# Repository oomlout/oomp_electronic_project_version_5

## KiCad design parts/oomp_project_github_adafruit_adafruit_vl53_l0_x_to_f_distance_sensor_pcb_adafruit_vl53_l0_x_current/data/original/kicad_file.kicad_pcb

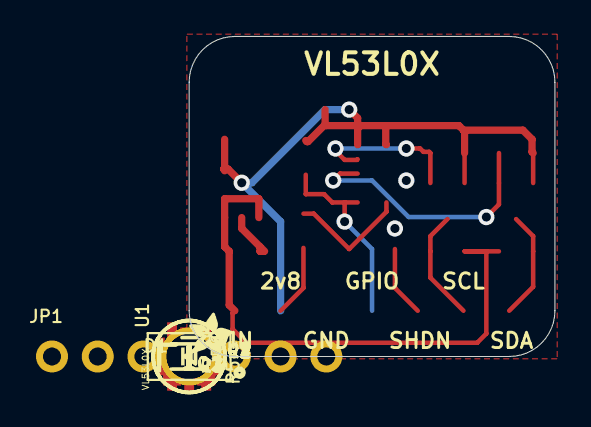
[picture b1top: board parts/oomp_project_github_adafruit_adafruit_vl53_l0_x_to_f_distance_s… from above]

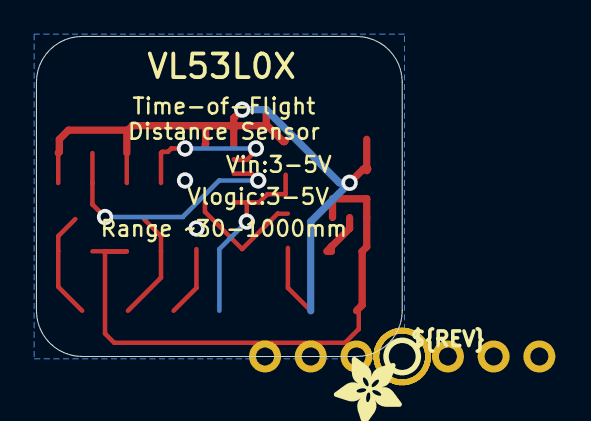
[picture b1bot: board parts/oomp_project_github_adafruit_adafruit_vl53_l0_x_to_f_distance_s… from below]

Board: 2 copper layers, 20.3 x 17.8 mm, 22 parts (2 on the bottom side), 10 nets.

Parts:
C1, C2: 10µF; 0805-NO
C3: 0.1uF; 0805-NO
D1: 1N4148; SOD-323
FID2, FID3: FIDUCIAL""; FIDUCIAL_1MM
JP1: 1X07_ROUND_70
Q1, Q2: BSS138; SOT23-WIDE
R1, R2, R3, R4, R5, R6: 10K; 0805-NO
U1: VL53L0X; LGA12_ST
U2: MIC5225_2.8V; SOT23-5
U$12: PCBFEAT-REV-040
U$13, U$14: MOUNTINGHOLE2.5; MOUNTINGHOLE_2.5_PLATED
U$15: ADAFRUIT_3.5MM
U$18: ADAFRUIT_2.5MM

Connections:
2.8V: C2.1, C3.1, JP1.2, Q1.1, Q2.1, R1.2, R2.2, R5.2, R6.2, U1.1, U1.11, U2.5
GND: C1.2, C2.2, C3.2, JP1.3, U1.2, U1.3, U1.4, U1.6, U1.12, U2.2
GPIO: JP1.4, R6.1, U1.7
SCL: JP1.6, Q2.3, R4.1
SCL_2.8V: Q2.2, R2.1, U1.10
SDA: JP1.7, Q1.3, R3.1
SDA_2.8V: Q1.2, R1.1, U1.9
VIN: C1.1, JP1.1, R3.2, R4.2, U2.1, U2.3
XSHUT: D1.C, JP1.5
XSHUT_2.8V: D1.A, R5.1, U1.5

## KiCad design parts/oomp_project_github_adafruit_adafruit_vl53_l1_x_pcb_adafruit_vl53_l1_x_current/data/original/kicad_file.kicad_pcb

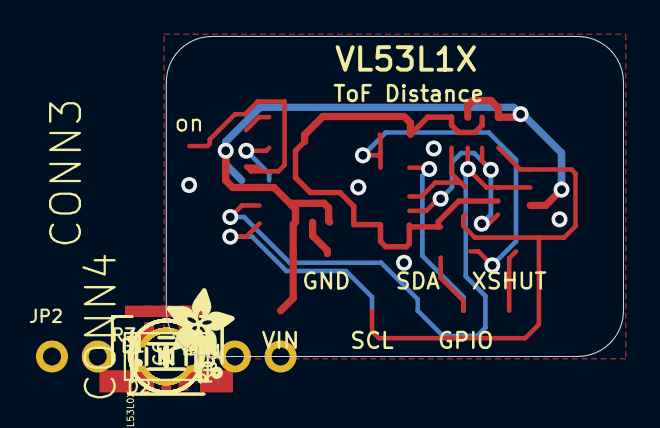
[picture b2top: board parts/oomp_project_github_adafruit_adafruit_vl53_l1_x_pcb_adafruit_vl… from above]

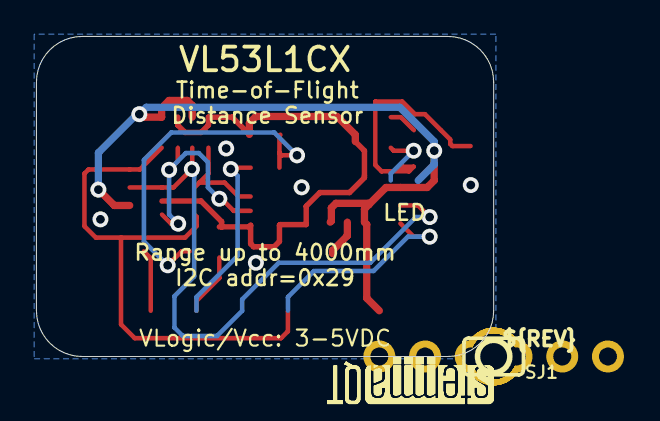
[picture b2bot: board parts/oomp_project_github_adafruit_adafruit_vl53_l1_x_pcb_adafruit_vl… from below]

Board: 2 copper layers, 25.4 x 17.8 mm, 26 parts (4 on the bottom side), 12 nets.

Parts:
C4, C5: 10uF; 0805-NO
C6: 0.1uF; 0603-NO
CONN3, CONN4: STEMMA_I2C_QT; JST_SH4
D1: 1N4148; SOD-323
D2: GREEN; CHIPLED_0603_NOOUTLINE
FID1, FID4: FIDUCIAL_1MM
JP2: 1X06_ROUND_70
Q3: BSS138; SOT363
R1, R2, R3: 10K; 0603-NO
R7: 10K; RESPACK_4X0603
SJ1: SOLDERJUMPER_CLOSEDWIRE
U1: VL53L0X; LGA12_ST
U3: LP5907-2.8; SOT23-5
U$30, U$31, U$33, U$34: MOUNTINGHOLE2.5; MOUNTINGHOLE_2.5_PLATED
U$36: ADAFRUIT_3.5MM
U$37: PCBFEAT-REV-040
U$38, U$39: STEMMAQT

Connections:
2.8V: C5.1, C6.1, Q3.2, Q3.5, R1.2, R2.2, R7.2, R7.4, U1.1, U1.11, U3.5
GND: C4.2, C5.2, C6.2, CONN3.1, CONN3.MT1, CONN3.MT2, CONN4.1, CONN4.MT1, CONN4.MT2, D2.C, JP2.2, U1.2, U1.3, U1.4, U1.6, U1.12, U3.2
GPIO: JP2.5, R2.1, U1.7
unnamed: D2.A, R3.1
unnamed: R3.2, SJ1.1
SCL: CONN3.4, CONN4.4, JP2.3, Q3.6, R7.8
SCL_3V: Q3.1, R7.7, U1.10
SDA: CONN3.3, CONN4.3, JP2.4, Q3.3, R7.6
SDA_3V: Q3.4, R7.5, U1.9
VCC: C4.1, CONN3.2, CONN4.2, JP2.1, R7.1, R7.3, SJ1.2, U3.1, U3.3
XSHUT: D1.C, JP2.6
XSHUT_2.8V: D1.A, R1.1, U1.5

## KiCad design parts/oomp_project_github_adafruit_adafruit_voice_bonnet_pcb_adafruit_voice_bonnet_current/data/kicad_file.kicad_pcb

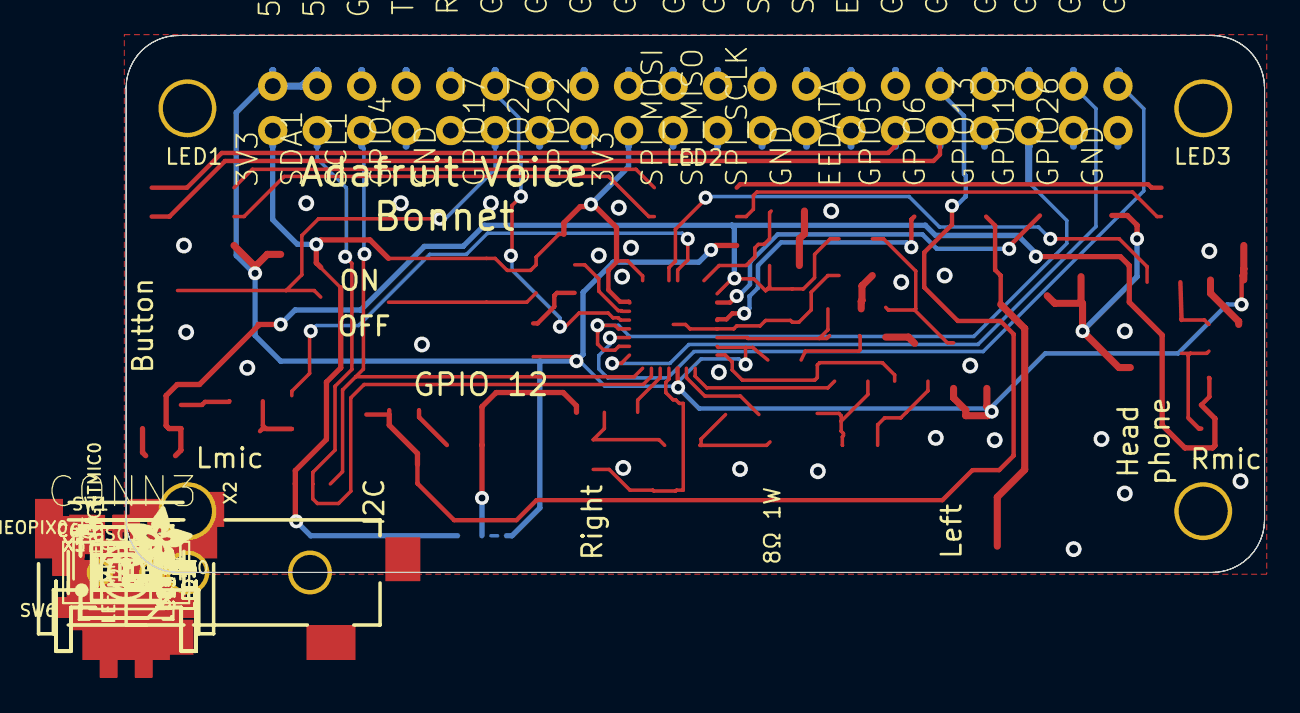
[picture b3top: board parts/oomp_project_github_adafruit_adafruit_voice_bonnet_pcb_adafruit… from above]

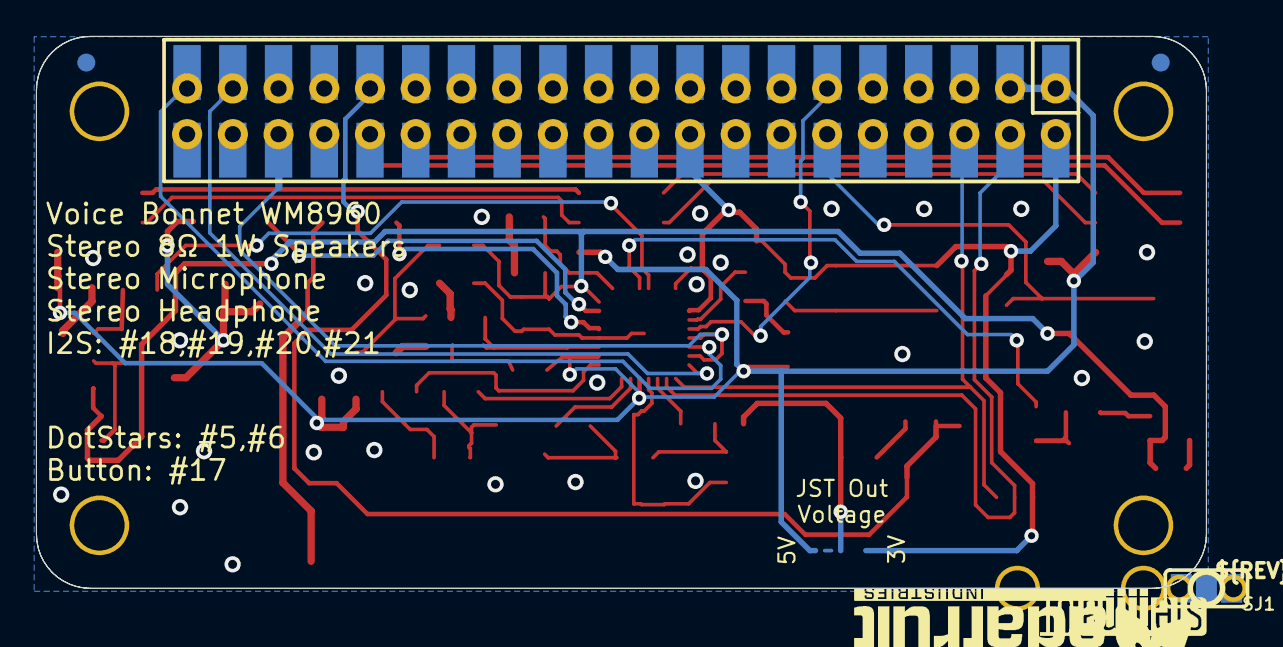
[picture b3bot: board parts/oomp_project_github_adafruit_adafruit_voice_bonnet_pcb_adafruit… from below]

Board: 2 copper layers, 65.0 x 30.7 mm, 69 parts (5 on the bottom side), 62 nets.

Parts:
C1, C2, C5, C9, C10, C11, C13, C23, C24, C32, C34: 10uF; 0805-NO
C3, C7, C8, C12, C14, C16, C18, C25: 0.1uF; 0603-NO
C4, C6: 100uF; PANASONIC_C
C19, C20, C21, C22: 33pF; 0603-NO
C26, C27: 220pF; 0603-NO
C28, C29, C30, C31: 100pF; 0603-NO
C33: 2.2uF+; 0805-NO
CONN3: STEMMA_I2C_QT; JST_SH4
D1: 3.6V; SOD-323
FB1, FB2: Ferrite; 0805
FB3: Ferrite; 0805-NO
FB4: FERRITE; 0805-NO
FB7, FB8, FB9, FB10: 120o; 0805-NO
FID1, FID2: FIDUCIAL_1MM
IC3: WM8960; QFN32_5MM
LED1, LED2, LED3: SK6822; APA102
LEFTMIC0: SPW2430HR5H-B
NEOPIX0: JST PH 3; JSTPH3
OSC1: ECS-3225MV; OSC_3.2X2.5MM
R1, R4: 10K; 0603-NO
R6: 10k; 0603-NO
R7: 1K; 0603-NO
RIGHTMIC0: SPW2430HR5H-B
RPI1: RASPBERRYPI_BPLUS_BONNET_THMSMT; PI_BONNET_THMSMT
SJ1: SOLDERJUMPER_2WAY_OPEN_NOPASTE
SW1: EVQQ; EVQ-Q2_SMALLER
SW6: EG1390
U3: AP2112-3.3K; SOT23-5
U$11: PCBFEAT-REV-040
U$12: STEMMAQT
U$15: ADAFRUIT_3.5MM
U$16: ADAFRUIT_TEXT_20MM
U$79: BRAINPAD_1IN
X1, X5: JSTPH 2P; JSTPH2
X2: 3.5mm; 4UCONN_19269

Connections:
3.3V: C12.1, CONN3.2, IC3.8, IC3.10, OSC1.4, R1.2, RPI1.1, RPI1.17, RPI1.S1, RPI1.S17, SJ1.3, SW6.S1, SW6.S2
5.0V: C9.1, C10.1, C11.1, C32.1, C33.1, IC3.21, IC3.26, LED1.4, LED2.4, LED3.4, RPI1.2, RPI1.4, RPI1.S2, RPI1.S4, SJ1.1, U3.1, U3.3
AGND: C3.2, C5.2, FB2.1, IC3.28, IC3.33
AVDD: C3.1, C5.1, C16.1, C18.1, C25.1, FB1.1, IC3.32, LEFTMIC0.4, RIGHTMIC0.4
BUTTON: R1.1, RPI1.11, RPI1.S11, SW1.B, SW1.B'
CE0: RPI1.24, RPI1.S24
CE1: RPI1.26, RPI1.S26
EEC: RPI1.28, RPI1.S28
EED: RPI1.27, RPI1.S27
GND: C1.2, C2.2, C7.2, C8.2, C9.2, C10.2, C11.2, C12.2, C13.2, C14.2, C16.2, C18.2, C19.2, C20.2, C21.2, C22.2, C25.2, C26.2, C27.2, C28.2, C29.2, C30.2, C31.2, C32.2, C33.2, C34.2, CONN3.1, D1.A, FB2.2, IC3.9, IC3.20, IC3.24, LED1.3, LED2.3, LED3.3, LEFTMIC0.2, LEFTMIC0.3, NEOPIX0.1, OSC1.2, R4.1, R6.1, RIGHTMIC0.2, RIGHTMIC0.3, RPI1.6, RPI1.9, RPI1.14, RPI1.20, RPI1.25, RPI1.30, RPI1.34, RPI1.39, RPI1.S6, RPI1.S9, RPI1.S14, RPI1.S20, RPI1.S25, RPI1.S30, RPI1.S34, RPI1.S39, SW1.A, SW1.A', SW6.O1, SW6.O2, U3.2, X2.1
GPIO4: RPI1.7, RPI1.S7
GPIO13: RPI1.33, RPI1.S33
GPIO19: RPI1.36, RPI1.S36
GPIO22: RPI1.15, RPI1.S15
GPIO23: RPI1.16, RPI1.S16
GPIO24: RPI1.18, RPI1.S18
GPIO25: RPI1.22, RPI1.S22
GPIO26: RPI1.37, RPI1.S37
GPIO27: RPI1.13, RPI1.S13
I2S_BCLK: IC3.12, RPI1.12, RPI1.S12
I2S_DIN: IC3.16, RPI1.38, RPI1.S38
I2S_DOUT: IC3.14, RPI1.40, RPI1.S40
I2S_LRCLK: IC3.13, IC3.15, RPI1.35, RPI1.S35
LEDC: LED1.2, RPI1.31, RPI1.S31
LEDD: LED1.1, RPI1.29, RPI1.S29
LEFT: C4.-, C27.1, R4.2, X2.2, X2.4
LEFT_N: C31.1, FB10.2, X1.2
LEFT_P: C30.1, FB9.2, X1.1
LINPUT1: C23.2, IC3.4
LSTEMMA: NEOPIX0.3, R7.1
MCLK: IC3.11, OSC1.3
MCLK_EN: OSC1.1, SW6.P1, SW6.P2
MICBIAS: C2.1, C8.1, IC3.1
MISO: RPI1.21, RPI1.S21
MOSI: RPI1.19, RPI1.S19
unnamed: FB7.1, IC3.19
unnamed: FB8.1, IC3.22
unnamed: C6.+, IC3.29
unnamed: C4.+, IC3.31
unnamed: LED1.6, LED2.1
unnamed: LED1.5, LED2.2
unnamed: C19.1, FB3.1, RIGHTMIC0.1
unnamed: C20.1, FB4.1, LEFTMIC0.1
unnamed: LED2.6, LED3.1
unnamed: LED2.5, LED3.2
unnamed: C21.1, C24.1, FB3.2
unnamed: C22.1, C23.1, FB4.2
unnamed: FB9.1, IC3.25
unnamed: FB10.1, IC3.23
OUT: C13.1, C14.1, FB1.2, U3.5
PWM0: D1.C, R7.2, RPI1.32, RPI1.S32
RIGHT: C6.-, C26.1, R6.2, X2.3, X2.5
RIGHT_N: C28.1, FB7.2, X5.2
RIGHT_P: C29.1, FB8.2, X5.1
RINPUT1: C24.2, IC3.5
RXD: RPI1.10, RPI1.S10
SCL: CONN3.4, IC3.17, RPI1.5, RPI1.S5
SCLK: RPI1.23, RPI1.S23
SDA: CONN3.3, IC3.18, RPI1.3, RPI1.S3
TXD: RPI1.8, RPI1.S8
VCC: C34.1, NEOPIX0.2, SJ1.2
VMID: C1.1, C7.1, IC3.27

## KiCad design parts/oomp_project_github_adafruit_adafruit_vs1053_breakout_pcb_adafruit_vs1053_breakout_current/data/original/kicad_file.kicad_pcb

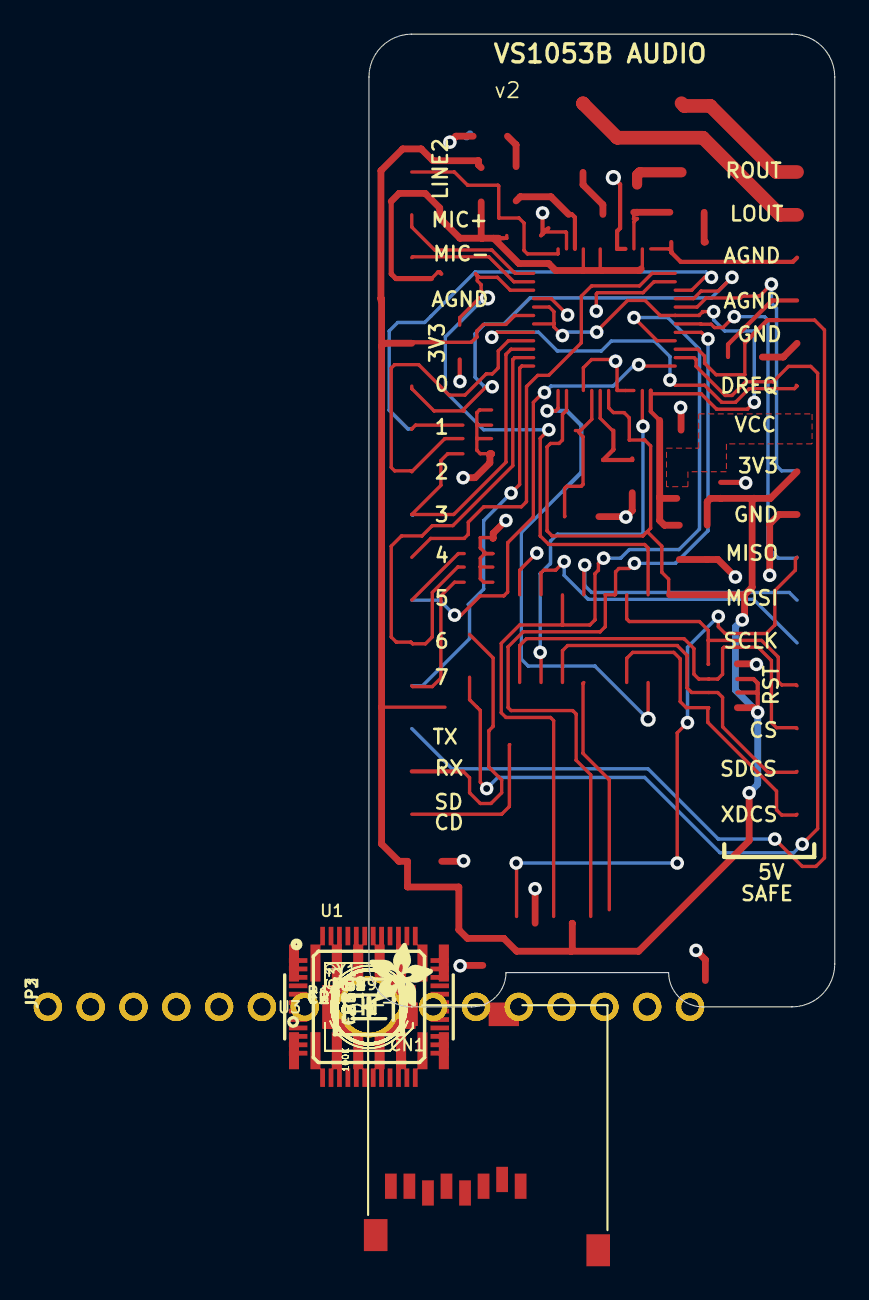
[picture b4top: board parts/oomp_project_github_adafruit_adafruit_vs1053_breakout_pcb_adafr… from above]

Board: 2 copper layers, 27.6 x 57.7 mm, 40 parts (1 on the bottom side), 45 nets.

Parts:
C1, C2: 220uF; PANASONIC_C
C4, C5: 10pF; _0805MP
C6, C7, C19, C20: 10µF; _0805MP
C8, C26: 0.1µF; _0805MP
C21, C22: 10nF (0.01uF); _0805MP
CN1: 2908-05WB-M6; MICROSD
D1: 1N4148; SOD-323
FB1, FB2: FERITTE; _0805MP
FID1, FID2: FIDUCIAL""; FIDUCIAL_1MM
JP2, JP3: 1X16_ROUND
R1: 1M; _0805MP
R2: 100K; _0805MP
R3, R4: 20; _0805MP
R6, R7: 100; _0805MP
R8, R9, R16: 100K; RESPACK_4X0603
R10: 10K; 0805-NO
U1: VS1053B; LQFP48
U2: AP7312-1833W6-7; SOT23-6
U3: 74HC4050D; SOIC16
U$31: ADAFRUIT_3.5MM
U$50, U$51, U$52, U$53: MOUNTINGHOLE3.0THIN; MOUNTINGHOLE_3.0_PLATEDTHIN
U$55: ADAFRUIT_TEXT_20MM
Y1: ABM8G-12.288MHZ-4Y-T3; CRYSTAL_3.2X2.5

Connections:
1.8V: C6.1, U1.5, U1.7, U1.24, U1.31, U2.6
3.3V: C7.1, C19.1, CN1.4, FB1.1, JP2.8, JP3.5, R9.5, R9.6, R9.7, R10.2, U1.6, U1.14, U1.19, U1.32, U2.1, U3.1
AGND: C8.2, C21.2, C22.2, FB2.2, JP2.3, JP2.4, JP3.4, U1.37, U1.40, U1.41, U1.47
AVDD: C8.1, FB1.2, R2.1, U1.38, U1.43, U1.45
CS_3V: U1.23, U3.10
CS_5V: JP2.14, R9.2, U3.9
DREQ: JP2.6, U1.8
GND: C4.2, C5.2, C6.2, C7.2, C19.2, C20.2, C26.2, CN1.6, CN1.MT1, CN1.MT2, FB2.1, JP2.5, JP2.9, R8.5, R8.6, R8.7, R8.8, R9.8, R16.5, R16.6, R16.7, R16.8, U1.4, U1.16, U1.20, U1.21, U1.22, U1.35, U2.2, U3.8
GPIO0: JP3.6, R16.1, U1.33
GPIO1: JP3.7, R16.2, U1.34
GPIO2: JP3.8, R16.3, U1.9
GPIO3: JP3.9, R16.4, U1.10
GPIO4: JP3.10, R8.1, U1.36
GPIO5: JP3.11, R8.2, U1.25
GPIO6: JP3.12, R8.3, U1.11
GPIO7: JP3.13, R8.4, U1.12
LEFT: R3.1, R7.2, U1.46
LEFT_FILTERED: C2.+, R7.1
LINE2: JP3.1, U1.48
L_OUT: C2.-, JP2.2
MIC_N: JP3.3, U1.2
MIC_P: JP3.2, U1.1
MISO: CN1.7, JP2.10, U1.30
MOSI_3V: CN1.3, U1.29, U3.4
MOSI_5V: JP2.11, U3.5
unnamed: C5.1, R1.1, U1.17, Y1.1
unnamed: C4.1, R1.2, U1.18, Y1.2
unnamed: C21.1, R3.2
unnamed: C22.1, R4.2
RIGHT: R4.1, R6.2, U1.39
RIGHT_FILTERED: C1.+, R6.1
RST_3V: C26.1, R2.2, U1.3, U3.2
RST_5V: JP2.13, R9.1, U3.3
RX: D1.A, R10.1, U1.26
RX_5V: D1.C, JP3.15
R_OUT: C1.-, JP2.1
SCLK_3V: CN1.5, U1.28, U3.6
SCLK_5V: JP2.12, U3.7
SDCS_3V: CN1.2, U3.12
SDCS_5V: JP2.15, R9.3, U3.11
SD_DETECT: CN1.CD1, JP3.16
TX: JP3.14, U1.27
VIN: C20.1, JP2.7, U2.3, U2.4, U2.5
XDCS_3V: U1.13, U3.15
XDCS_5V: JP2.16, R9.4, U3.14

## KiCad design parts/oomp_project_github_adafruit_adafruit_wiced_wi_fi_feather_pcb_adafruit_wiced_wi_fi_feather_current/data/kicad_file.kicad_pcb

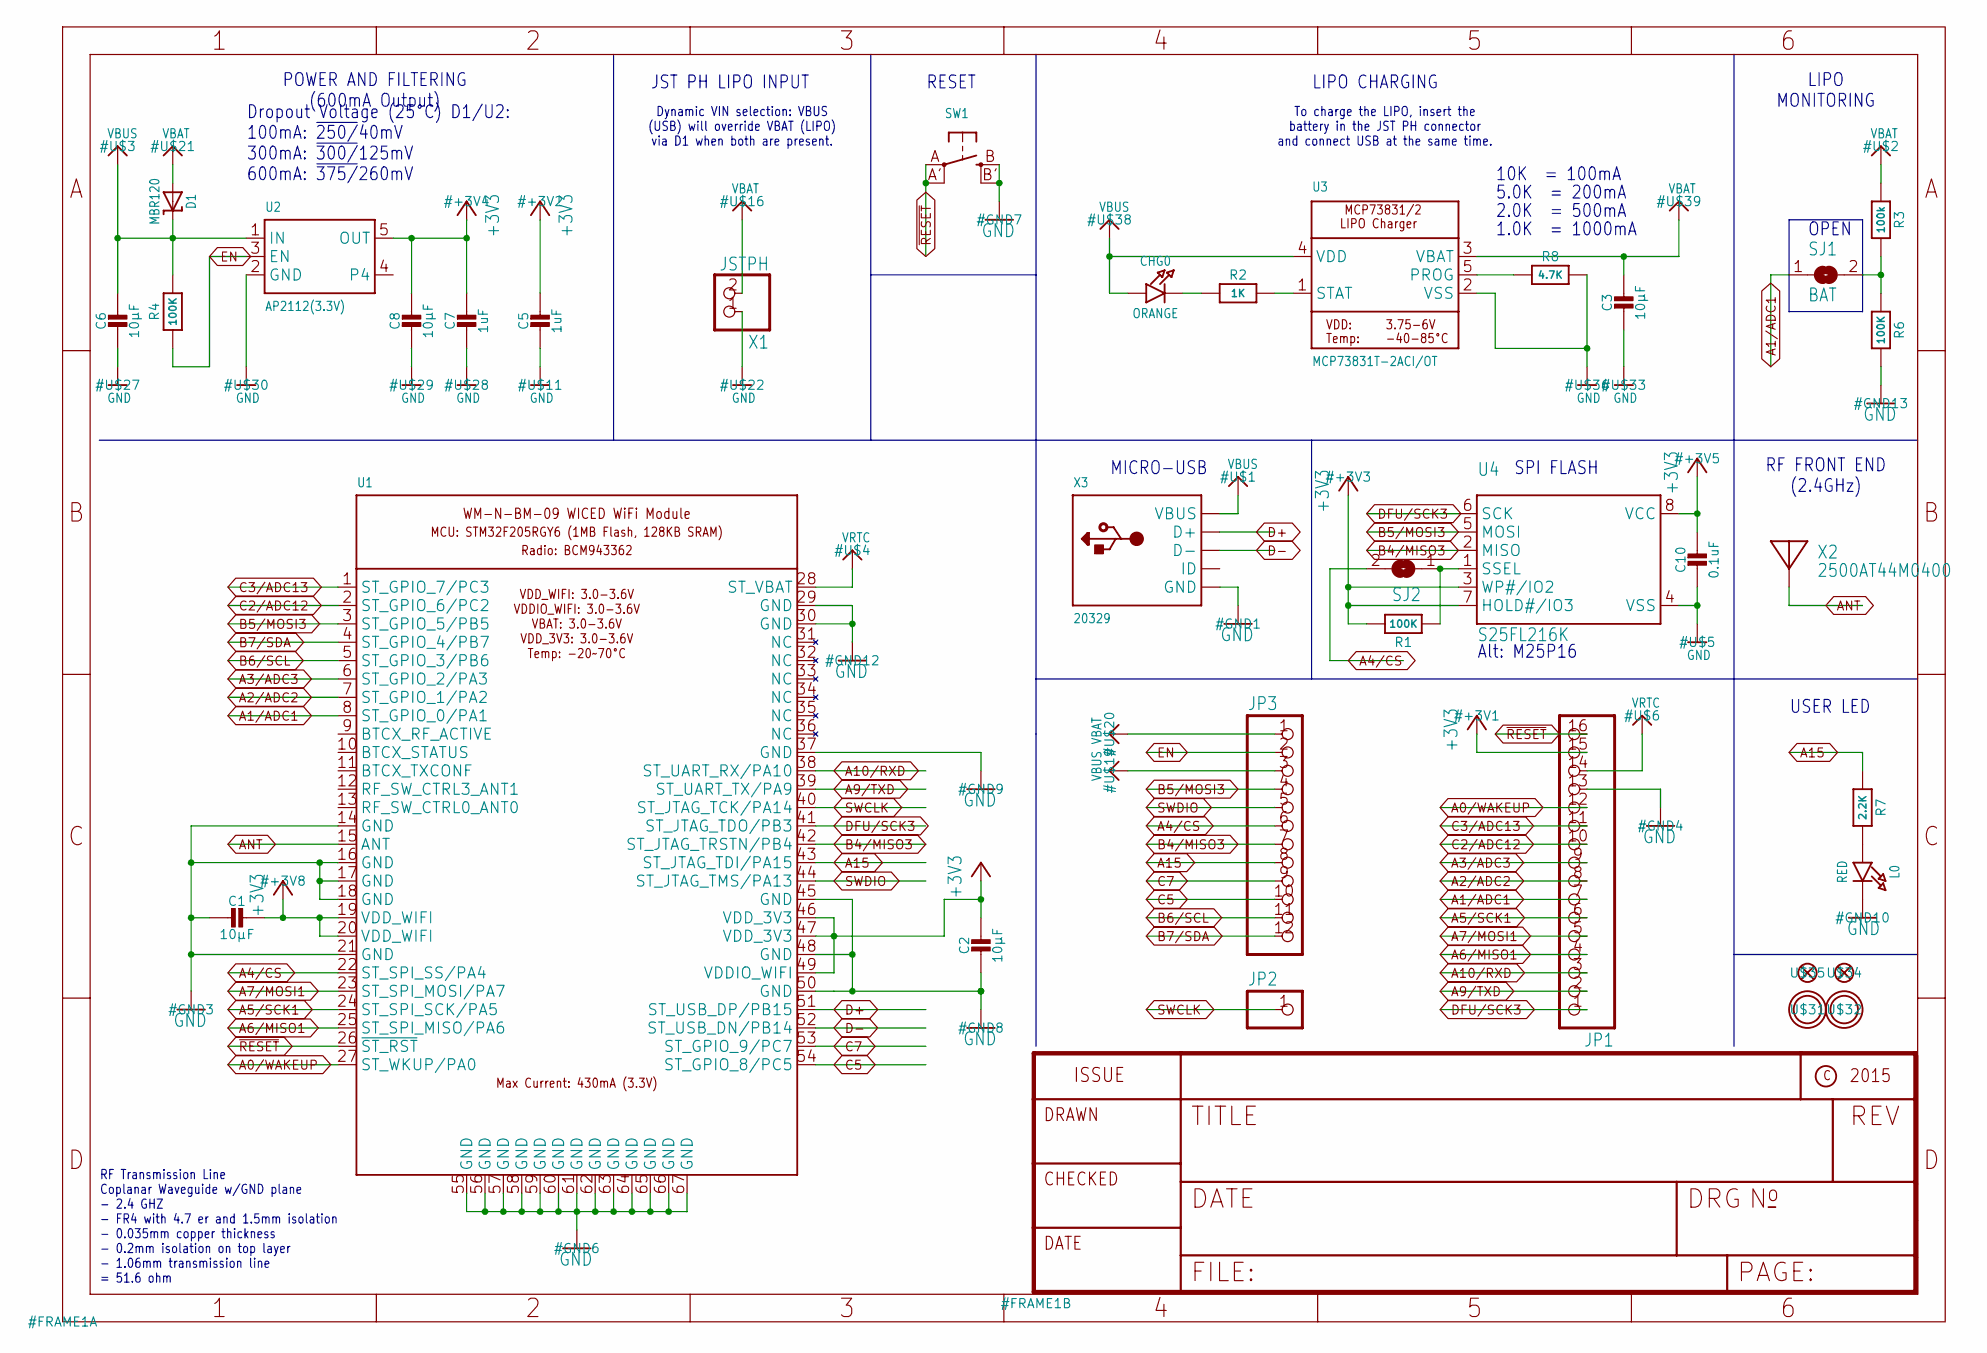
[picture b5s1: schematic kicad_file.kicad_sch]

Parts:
C1, C2, C3, C6, C8: 10µF; 0805-NO
C5, C7: 1uF; 0603-NO
C10: 0.1uF; 0805_10MGAP
CHG0: ORANGE; CHIPLED_0805_NOOUTLINE
D1: MBR120; SOD-123
JP1: HEADER-1X16ROUND; 1X16_ROUND
JP2: HEADER-1X1ROUND; 1X01_ROUND
JP3: HEADER-1X12; 1X12_ROUND
L0: RED; CHIPLED_0805_NOOUTLINE
R1, R4, R6: 100K; 0603-NO
R2: 1K; 0603-NO
R3: 100k; 0603-NO
R7: 2.2K; 0603-NO
R8: 4.7K; 0603-NO
SJ1: BAT; SOLDERJUMPER_REFLOW_NOPASTE
SJ2: SOLDERJUMPER; SOLDERJUMPER_ARROW_NOPASTE
SW1: SWITCH_TACT_SMT4.6X2.8; BTN_KMR2_4.6X2.8
U1: USI_WM-N-BM-09
U2: AP2112(3.3V); SOT23-5
U3: MCP73831T-2ACI/OT; SOT23-5
U4: S25FL216K; SOIC8_150MIL
U$31, U$32: MOUNTINGHOLE2.5; MOUNTINGHOLE_2.5_PLATED
U$34, U$35: FIDUCIAL""; FIDUCIAL_1MM
X1: JSTPH; JSTPH2
X2: 2500AT44M0400; ANT_2500AT44M0400
X3: 20329; 4UCONN_20329_V2

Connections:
+3V3: C1.1, C2.1, C5.1, C7.1, C8.1, C10.1, JP1.15, R1.2, U1.19 (VDD_WIFI), U1.20 (VDD_WIFI), U1.46 (VDD_3V3), U1.47 (VDD_3V3), U1.49 (VDDIO_WIFI), U2.5 (OUT), U4.3 (WP#/IO2), U4.7 (HOLD#/IO3), U4.8 (VCC)
A0/WAKEUP: JP1.12, U1.27 (ST_WKUP/PA0)
A1/ADC1: JP1.7, SJ1.1, U1.8 (ST_GPIO_0/PA1)
A2/ADC2: JP1.8, U1.7 (ST_GPIO_1/PA2)
A3/ADC3: JP1.9, U1.6 (ST_GPIO_2/PA3)
A4/CS: JP3.6, SJ2.2, U1.22 (ST_SPI_SS/PA4)
A5/SCK1: JP1.6, U1.24 (ST_SPI_SCK/PA5)
A6/MISO1: JP1.4, U1.25 (ST_SPI_MISO/PA6)
A7/MOSI1: JP1.5, U1.23 (ST_SPI_MOSI/PA7)
A9/TXD: JP1.2, U1.39 (ST_UART_TX/PA9)
A10/RXD: JP1.3, U1.38 (ST_UART_RX/PA10)
A15: JP3.8, R7.1, U1.43 (ST_JTAG_TDI/PA15)
ANT: U1.15 (ANT), X2.FEED
B4/MISO3: JP3.7, U1.42 (ST_JTAG_TRSTN/PB4), U4.2 (MISO)
B5/MOSI3: JP3.4, U1.3 (ST_GPIO_5/PB5), U4.5 (MOSI)
B6/SCL: JP3.11, U1.5 (ST_GPIO_3/PB6)
B7/SDA: JP3.12, U1.4 (ST_GPIO_4/PB7)
C2/ADC12: JP1.10, U1.2 (ST_GPIO_6/PC2)
C3/ADC13: JP1.11, U1.1 (ST_GPIO_7/PC3)
C5: JP3.10, U1.54 (ST_GPIO_8/PC5)
C7: JP3.9, U1.53 (ST_GPIO_9/PC7)
D+: U1.51 (ST_USB_DP/PB15), X3.D+
D-: U1.52 (ST_USB_DN/PB14), X3.D-
DFU/SCK3: JP1.1, U1.41 (ST_JTAG_TDO/PB3), U4.6 (SCK)
EN: JP3.2, R4.1, U2.3 (EN)
GND: C1.2, C2.2, C3.2, C5.2, C6.2, C7.2, C8.2, C10.2, JP1.13, L0.C, R6.2, R8.2, SW1.B (S), SW1.B' (S1), U1.14 (GND), U1.16 (GND), U1.17 (GND), U1.18 (GND), U1.21 (GND), U1.29 (GND), U1.30 (GND), U1.37 (GND), U1.45 (GND), U1.48 (GND), U1.50 (GND), U1.55 (GND), U1.56 (GND), U1.57 (GND), U1.58 (GND), U1.59 (GND), U1.60 (GND), U1.61 (GND), U1.62 (GND), U1.63 (GND), U1.64 (GND), U1.65 (GND), U1.66 (GND), U1.67 (GND), U2.2 (GND), U3.2 (VSS), U4.4 (VSS), X1.1, X3.BASE@1 (GND), X3.BASE@2 (GND), X3.GND, X3.SPRT@1 (GND), X3.SPRT@2 (GND), X3.SPRT@3 (GND), X3.SPRT@4 (GND)
unnamed: CHG0.C, R2.1
unnamed: L0.A, R7.2
unnamed: R2.2, U3.1 (STAT)
unnamed: R8.1, U3.5 (PROG)
unnamed: R3.2, R6.1, SJ1.2
unnamed: R1.1, SJ2.1, U4.1 (SSEL)
SWCLK: JP2.1, U1.40 (ST_JTAG_TCK/PA14)
SWDIO: JP3.5, U1.44 (ST_JTAG_TMS/PA13)
VBAT: C3.1, D1.A, JP3.1, R3.1, U3.3 (VBAT), X1.2
VBUS: C6.1, CHG0.A, D1.C, JP3.3, R4.2, U2.1 (IN), U3.4 (VDD), X3.VBUS
VRTC: JP1.14, U1.28 (ST_VBAT)
~RESET: JP1.16, SW1.A, SW1.A' (P1), U1.26 (~ST_RST)

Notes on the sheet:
SPI FLASH
Dropout Voltage (25°C) D1/U2: 100mA: ~{250/}40mV 300mA: ~{300/}125mV 600mA: ~{375/}260mV
RF FRONT END (2.4GHz)
To charge the LIPO, insert the battery in the JST PH connector and connect USB at the same time.
LIPO CHARGING
RESET
1.0K = 1000mA
MICRO-USB
RF Transmission Line Coplanar Waveguide w/GND plane - 2.4 GHZ - FR4 with 4.7 er and 1.5mm isolation - 0.035mm copper thickness - 0.2mm isolation on top layer - 1.06mm transmission line = 51.6 ohm
10K = 100mA
LIPO MONITORING
2.0K = 500mA
Dynamic VIN selection: VBUS (USB) will override VBAT (LIPO) via D1 when both are present.
USER LED
OPEN
Alt: M25P16
JST PH LIPO INPUT
POWER AND FILTERING (600mA Output)
5.0K = 200mA

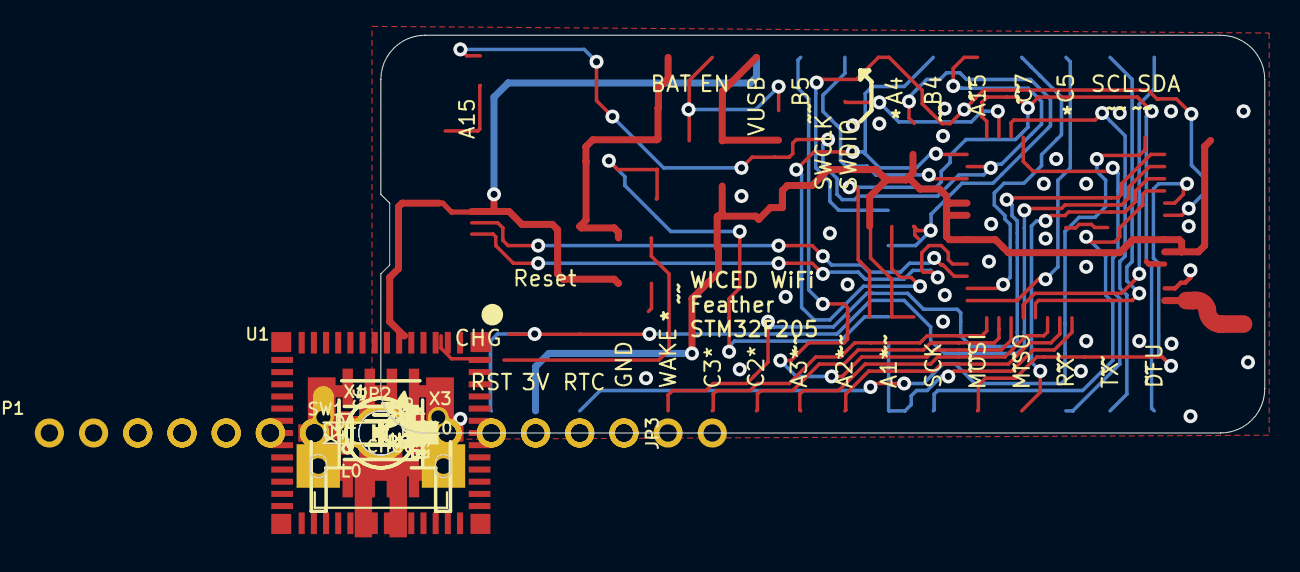
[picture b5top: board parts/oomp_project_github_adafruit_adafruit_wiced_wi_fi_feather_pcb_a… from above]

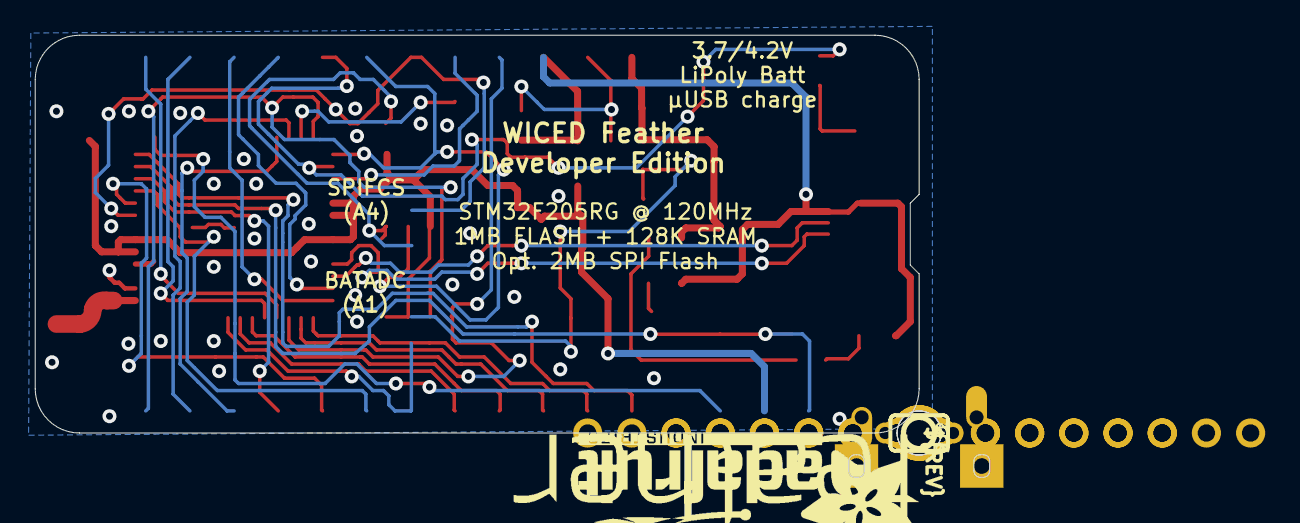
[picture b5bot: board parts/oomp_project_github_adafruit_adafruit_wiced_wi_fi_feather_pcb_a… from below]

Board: 2 copper layers, 50.8 x 22.9 mm, 41 parts (5 on the bottom side), 38 nets.

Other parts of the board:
U$7: FEATHERLOGO
U$8: ADAFRUIT_2.5MM
U$10: ADAFRUIT_TEXT_20MM
U$23: PCBFEAT-REV-040
UNK_HOLE_0: dummyfp0
UNK_HOLE_1: dummyfp1

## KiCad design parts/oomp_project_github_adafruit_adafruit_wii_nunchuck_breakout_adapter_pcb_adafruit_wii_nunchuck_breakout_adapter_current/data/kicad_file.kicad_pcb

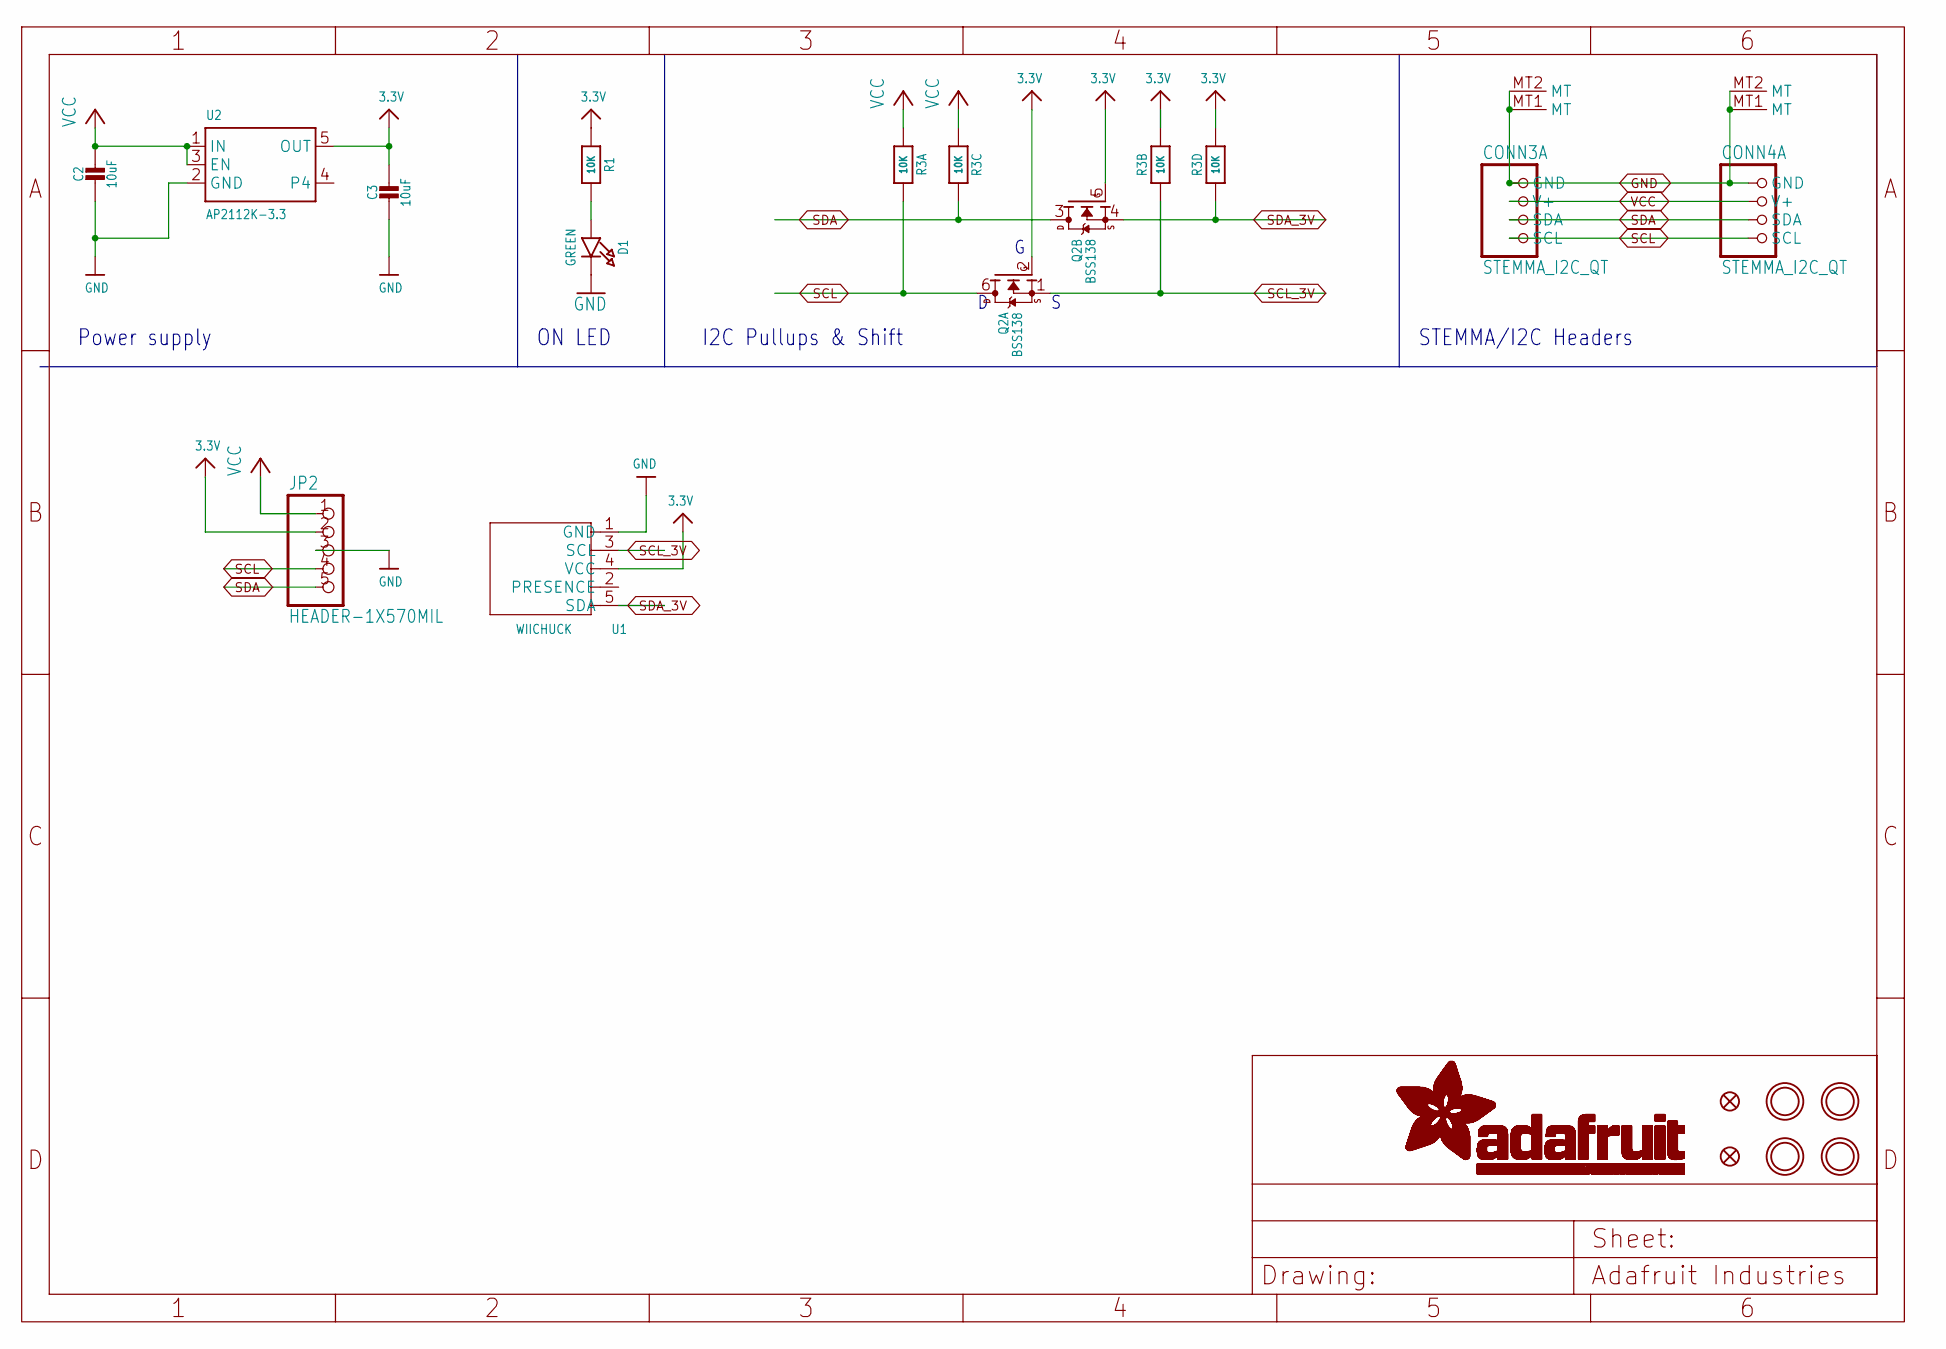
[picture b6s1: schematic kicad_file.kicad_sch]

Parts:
C2, C3: 10uF; 0805-NO
CONN3, CONN4: STEMMA_I2C_QT; JST_SH4
D1: GREEN; CHIPLED_0603_NOOUTLINE
FID3, FID4: FIDUCIAL_1MM
JP2: HEADER-1X570MIL; 1X05_ROUND_70
Q2: BSS138; SOT363
R1: 10K; 0603-NO
R3: 10K; RESPACK_4X0603
U1: WIICHUCK
U2: AP2112K-3.3; SOT23-5
U$1, U$17, U$19, U$21: MOUNTINGHOLE2.5; MOUNTINGHOLE_2.5_PLATED

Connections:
3.3V: C3.1, JP2.2, Q2.2 (G), Q2.5 (G), R1.1, R3.2 (1), R3.4 (1), U1.4 (VCC), U2.5 (OUT)
GND: C2.2, C3.2, CONN3.1 (GND), CONN3.MT1 (MT), CONN3.MT2 (MT), CONN4.1 (GND), CONN4.MT1 (MT), CONN4.MT2 (MT), D1.C, JP2.3, U1.1 (GND), U2.2 (GND)
unnamed: D1.A, R1.2
SCL: CONN3.4 (SCL), CONN4.4 (SCL), JP2.4, Q2.6 (D), R3.8 (2)
SCL_3V: Q2.1 (S), R3.7 (2), U1.3 (SCL)
SDA: CONN3.3 (SDA), CONN4.3 (SDA), JP2.5, Q2.3 (D), R3.6 (2)
SDA_3V: Q2.4 (S), R3.5 (2), U1.5 (SDA)
VCC: C2.1, CONN3.2 (V+), CONN4.2 (V+), JP2.1, R3.1, R3.3 (1), U2.1 (IN), U2.3 (EN)

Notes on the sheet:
STEMMA/I2C Headers
Power supply
I2C Pullups & Shift
ON LED

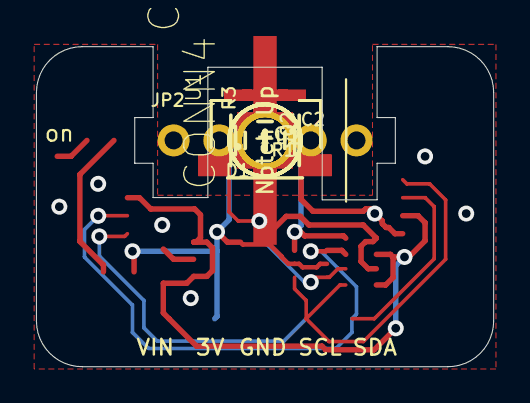
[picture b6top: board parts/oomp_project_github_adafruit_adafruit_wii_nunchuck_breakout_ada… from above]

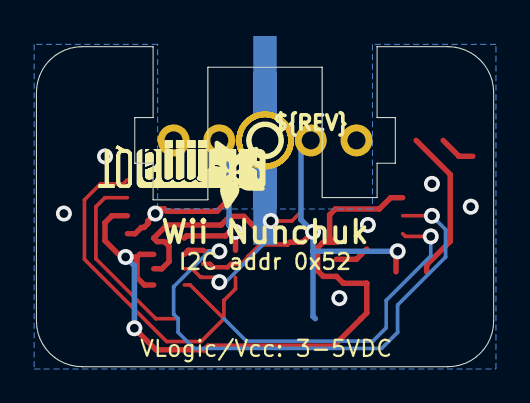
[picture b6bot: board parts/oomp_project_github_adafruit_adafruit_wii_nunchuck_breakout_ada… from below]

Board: 2 copper layers, 25.4 x 17.8 mm, 21 parts (4 on the bottom side), 8 nets.

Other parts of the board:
U$22: ADAFRUIT_3.5MM
U$25: PCBFEAT-REV-040
U$30, U$31: STEMMAQT

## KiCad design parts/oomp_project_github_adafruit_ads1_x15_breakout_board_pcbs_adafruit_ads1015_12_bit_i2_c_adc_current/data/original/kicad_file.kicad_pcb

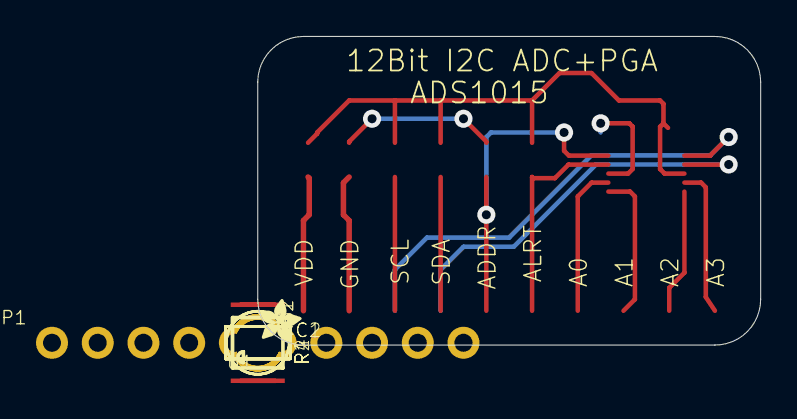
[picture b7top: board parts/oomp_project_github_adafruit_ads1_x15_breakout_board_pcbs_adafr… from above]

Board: 2 copper layers, 27.9 x 17.1 mm, 16 parts (1 on the bottom side), 12 nets.

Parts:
C1, C2: 10µF; 0805
FB1, FB2: FERRITE; 0805
FID1, FID2: FIDUCIAL""; FIDUCIAL_1MM
JP1: 1X10_ROUND70
R1, R2, R3, R4: 10K; 0805
U1: ADS1015IDGST; MSOP10
U$13, U$14: MOUNTINGHOLE2.5; MOUNTINGHOLE_2.5_PLATED
U$15: ADAFRUIT_TEXT_20MM
U$16: ADAFRUIT_2.5MM

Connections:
ADDR: JP1.6, R3.1, U1.1
AIN0: JP1.4, U1.4
AIN1: JP1.3, U1.5
AIN2: JP1.2, U1.6
AIN3: JP1.1, U1.7
ALERT: JP1.5, R4.2, U1.2
GND: C1.1, FB2.2, R3.2, U1.3
unnamed: C2.1, FB1.1, JP1.10
unnamed: C2.2, FB2.1, JP1.9
SCL: JP1.8, R1.2, U1.10
SDA: JP1.7, R2.2, U1.9
VDD: C1.2, FB1.2, R1.1, R2.1, R4.1, U1.8
